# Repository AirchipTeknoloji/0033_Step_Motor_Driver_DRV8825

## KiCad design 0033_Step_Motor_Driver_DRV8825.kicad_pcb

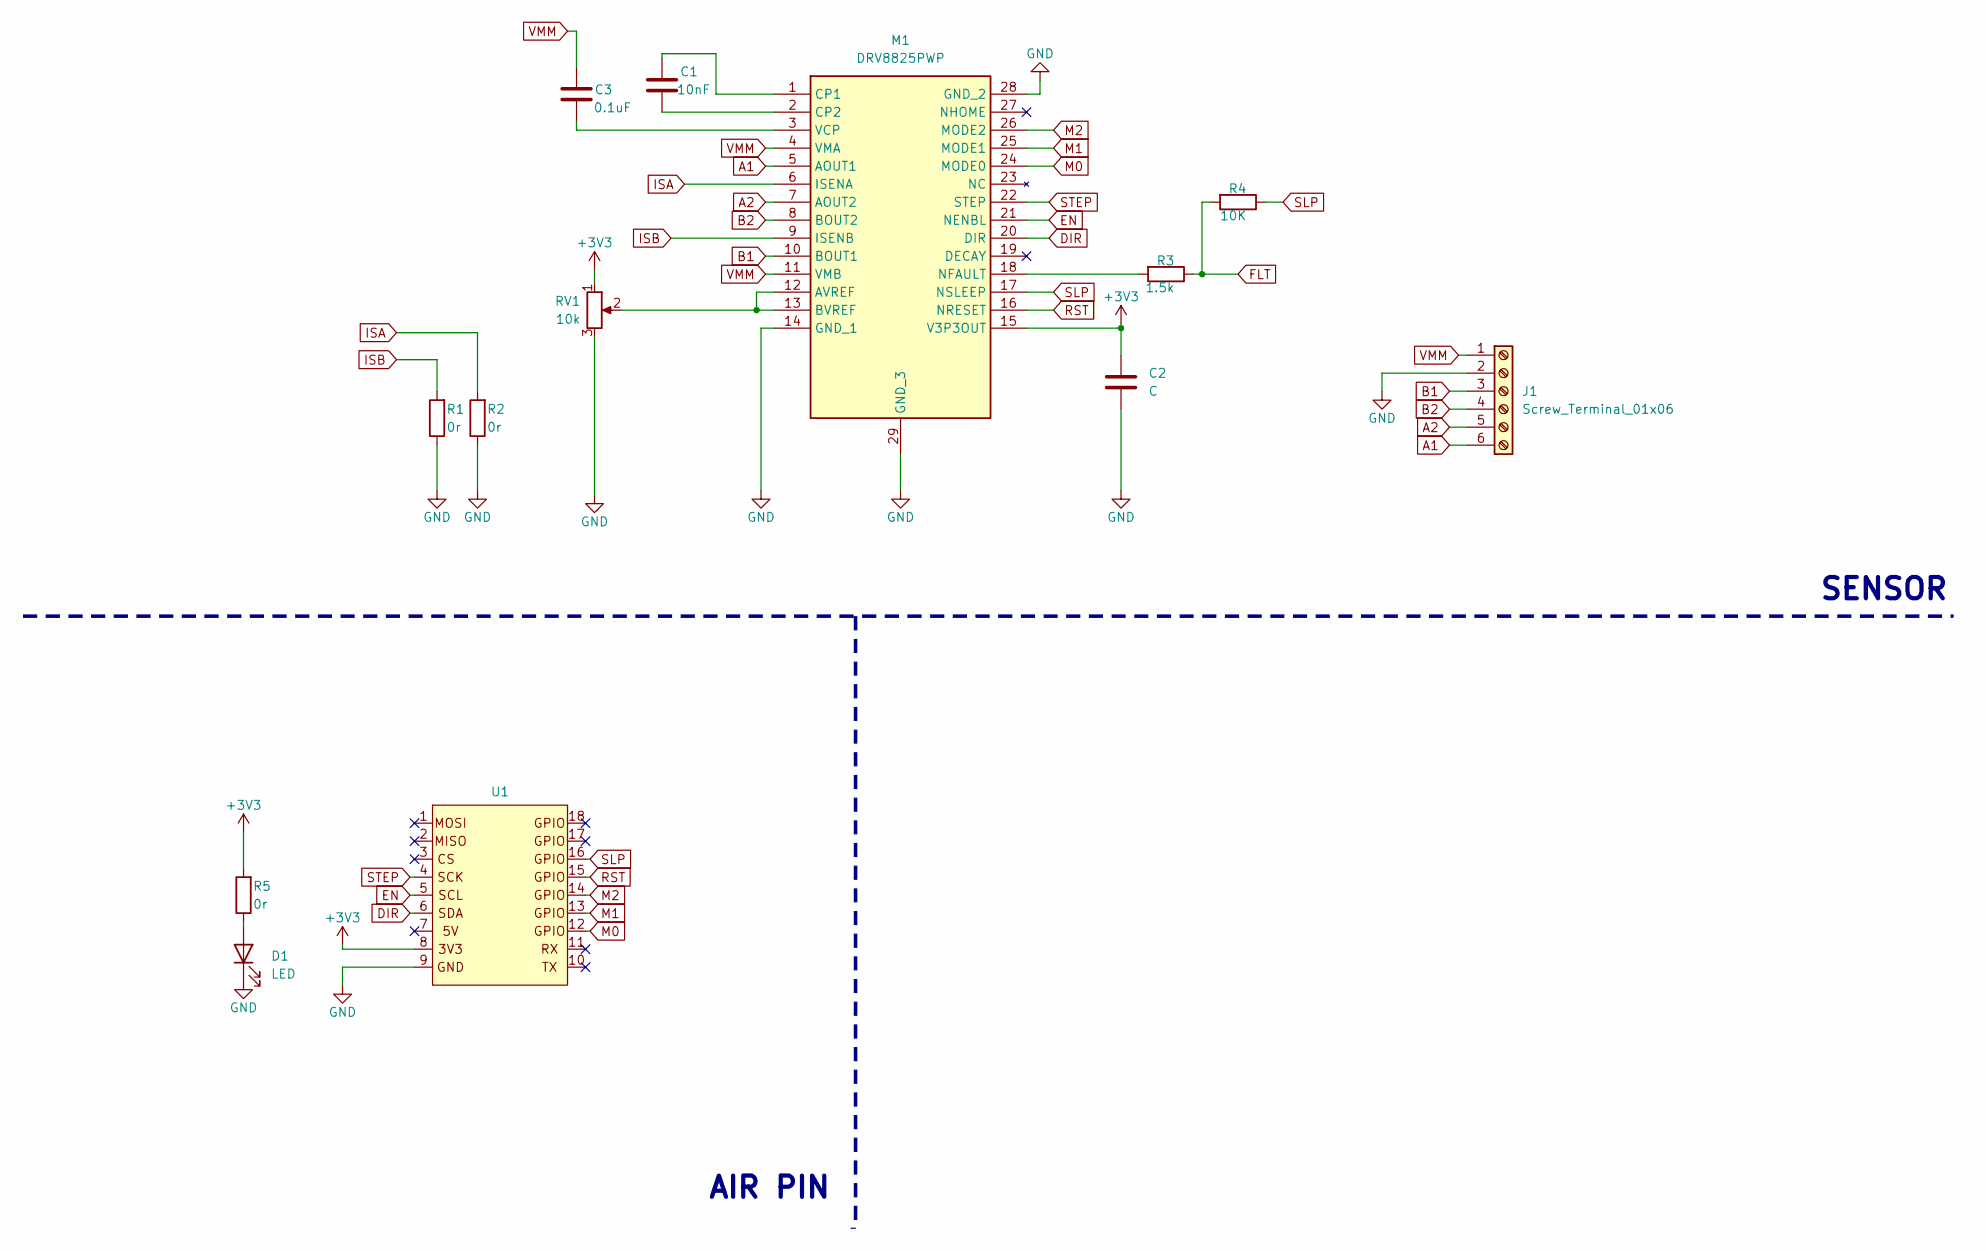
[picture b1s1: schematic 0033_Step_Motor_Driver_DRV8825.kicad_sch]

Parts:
C1: 10nF; C_0603_1608Metric
C2: C; C_0603_1608Metric
C3: 0.1uF; C_0603_1608Metric
D1: LED; LED_0805_2012Metric
J1: Screw_Terminal_01x06; PinHeader_1x06_P2.54mm_Vertical
M1: DRV8825PWP; SOP65P640X120-29N; Mouser Part Number 595-DRV8825PWP
R1, R2: 0r; R_0603_1608Metric
R3: 1.5k; R_0603_1608Metric
R4: 10K; R_0603_1608Metric
R5: 0r; R_0805_2012Metric
RV1: 10k; 3362P_1
U1: pin_header

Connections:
+3V3: C2.1, M1.15 (V3P3OUT), R5.2, RV1.1, U1.8; also elsewhere on the board
A1: J1.6, M1.5 (AOUT1)
A2: J1.5, M1.7 (AOUT2)
B1: J1.3, M1.10 (BOUT1)
B2: J1.4, M1.8 (BOUT2)
DIR: M1.20 (DIR), U1.6
EN: M1.21 (NENBL), U1.5
FLT: R3.1, R4.2
GND: C2.2, D1.1 (K), J1.2, M1.14 (GND_1), M1.28 (GND_2), M1.29 (GND_3), R1.1, R2.1, RV1.3, U1.9; also elsewhere on the board
ISA: M1.6 (ISENA), R2.2
ISB: M1.9 (ISENB), R1.2
M0: M1.24 (MODE0), U1.12
M1: M1.25 (MODE1), U1.13
M2: M1.26 (MODE2), U1.14
unnamed: D1.2 (A), R5.1
unnamed 15: M1.12 (AVREF), M1.13 (BVREF), RV1.2; also elsewhere on the board
unnamed: C1.2, M1.1 (CP1)
unnamed: C1.1, M1.2 (CP2)
unnamed: M1.18 (NFAULT), R3.2
unnamed: C3.1, M1.3 (VCP)
RST: M1.16 (NRESET), U1.15
SLP: M1.17 (NSLEEP), R4.1, U1.16
STEP: M1.22 (STEP), U1.4
VMM: C3.2, J1.1, M1.4 (VMA), M1.11 (VMB)

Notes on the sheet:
SENSOR
AIR PIN

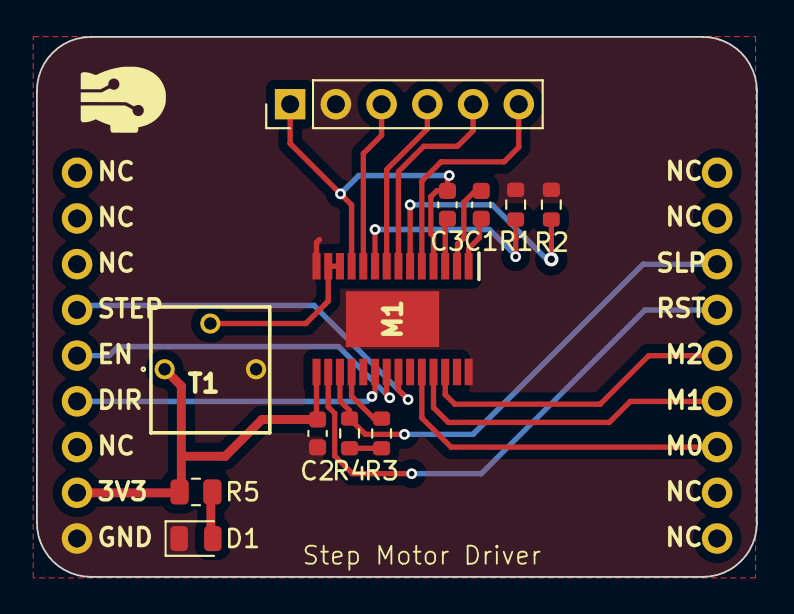
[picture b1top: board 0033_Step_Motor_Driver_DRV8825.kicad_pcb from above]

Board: 2 copper layers, 40.0 x 30.0 mm, 13 parts (0 on the bottom side), 24 nets.

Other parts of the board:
T1: 10k; 3362P_1

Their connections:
+3V3: T1.1; also elsewhere on the board
GND: T1.3; also elsewhere on the board
unnamed 15: T1.2; also elsewhere on the board
